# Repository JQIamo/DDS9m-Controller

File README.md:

# DDS9m-Controller
Interface PCB for Novatech DDS9m frequency generator

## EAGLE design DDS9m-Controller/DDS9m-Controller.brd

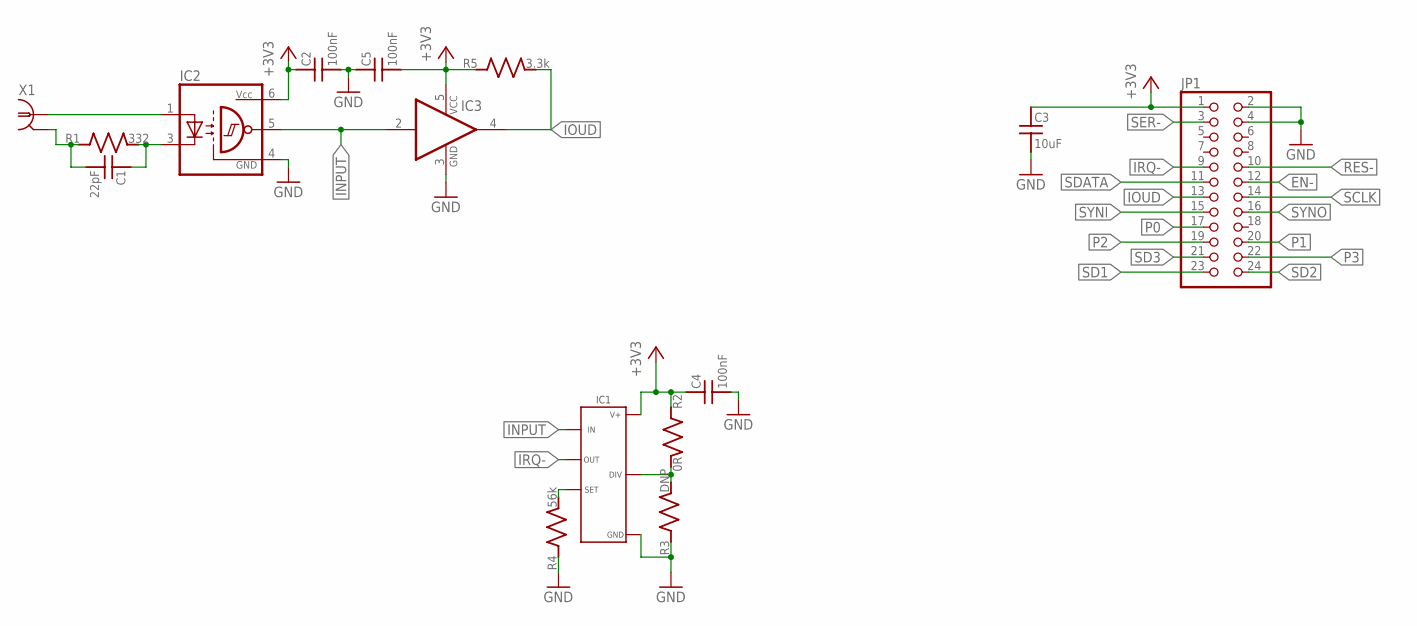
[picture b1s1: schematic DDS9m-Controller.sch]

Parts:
C1: 22pF; C_MLCC_0402; PARTNO CL05C220JB51PNC
C2, C4, C5: 100nF; C_MLCC_0603; PARTNO CL10B104KB8NNNC
C3: 10uF; C_MLCC_1210; PARTNO CL32B106KLJNNNE
IC1: LTC6994-X; SOT23-6L; PARTNO LTC6994IS6-2#TRMPBF
IC2: TLP2767; SO6L; PARTNO TLP2767(TP,E
IC3: 74LVC1G07DCK; SC70-5; PARTNO SN74LVC1G07DCKR
JP1: PINHD-2X12; 2X12; PARTNO PPPC122LFBN-RC
R1: 332; R_0603; PARTNO ERJ-3EKF3320V
R2: 0R; R_0603; PARTNO MF-RES-0603-0
R3: DNP; R_0603
R4: 56k; R_0603; PARTNO ERA-3AEB563V
R5: 3.3k; R_0603; PARTNO ERJ-3EKF3301V
X1: BNC-V; PARTNO 5227222-3

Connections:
+3V3: C2.P$1 (1), C3.P$1 (1), C4.P$1 (1), C5.P$2 (2), IC1.5 (V+), IC2.6 (VCC), IC3.5 (VCC), JP1.1, R2.P$1 (1), R5.P$1 (1)
EN-: JP1.12
GND: C2.P$2 (2), C3.P$2 (2), C4.P$2 (2), C5.P$1 (1), IC1.2 (GND), IC2.4 (GND), IC3.3 (GND), JP1.2, JP1.4, R3.P$1 (1), R4.P$1 (1)
INPUT: IC1.1 (IN), IC2.5 (OUT), IC3.2 (I)
IOUD: IC3.4 (O), JP1.13, R5.P$2 (2)
IRQ-: IC1.6 (OUT), JP1.9
unnamed: C1.P$1 (1), IC2.3 (C), R1.P$2 (2)
unnamed: C1.P$2 (2), R1.P$1 (1), X1.2
unnamed: IC2.1 (A), X1.1
unnamed: IC1.4 (DIV), R2.P$2 (2), R3.P$2 (2)
unnamed: IC1.3 (SET), R4.P$2 (2)
P0: JP1.17
P1: JP1.20
P2: JP1.19
P3: JP1.22
RES-: JP1.10
SCLK: JP1.14
SD1: JP1.23
SD2: JP1.24
SD3: JP1.21
SDATA: JP1.11
SER-: JP1.3
SYNI: JP1.15
SYNO: JP1.16

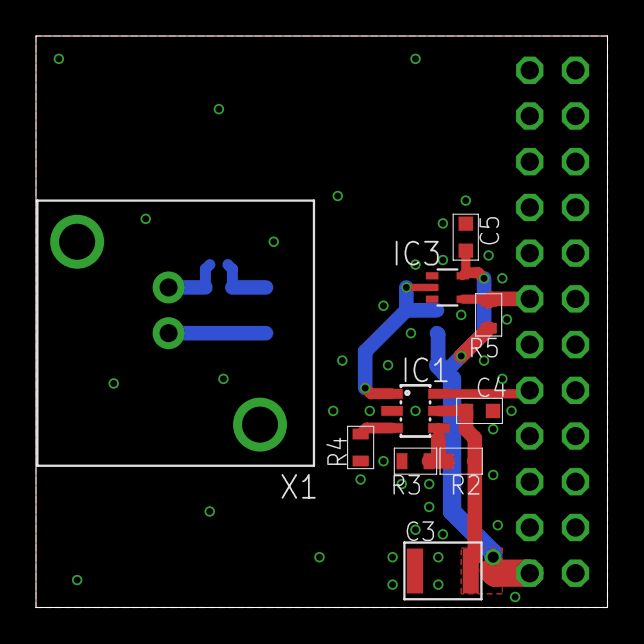
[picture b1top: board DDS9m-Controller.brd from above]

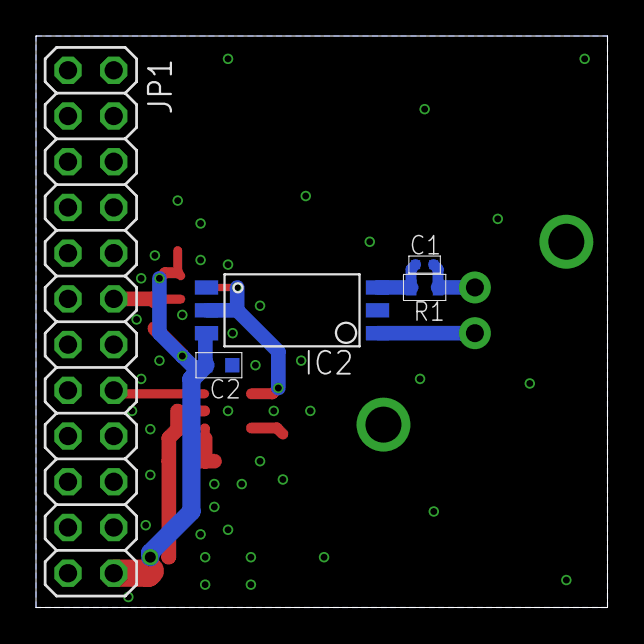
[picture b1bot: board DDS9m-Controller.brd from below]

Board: 2 copper layers, 31.8 x 31.8 mm, 15 parts (5 on the bottom side), 10 nets.

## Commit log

2019-08-23 Initial schematic
    First pass at the schematic for the DDS9m trigger circuit.
    DSB
2019-09-13 Finished test layout
    First pass at the schematic and board is ready to prototype.
    DSB
